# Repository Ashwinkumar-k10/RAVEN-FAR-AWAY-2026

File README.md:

# 🚁 RAVEN System (Rapid Autonomous Victim Emergency Network)

**RAVEN** is a next-generation, fully autonomous AI drone surveillance and emergency response system. Designed to dramatically reduce emergency response times, RAVEN utilizes edge-deployed computer vision and advanced Vision-Language Models (VLMs) to detect, verify, and broadcast severe vehicular collisions in real-time.

## 🌟 Key Features

- **Multi-Agent Verification Pipeline:** Utilizes a fine-tuned YOLOv8 model for real-time bounding box detection, cross-verified by a Moondream VLM to guarantee zero false positives on standing traffic.
- **Autonomous Emergency Dispatch:** Automatically assesses accident severity (Normal, Serious, Critical) and broadcasts live telemetry to the dashboard.
- **Live Command Center Dashboard:** A sleek, fully responsive HTML/JS command center featuring real-time WebSockets, OpenStreetMap integration, live video feeds, and an AI semantic analysis typewriter effect.
- **Text-to-Speech Status Updates:** Integrated Web Speech API provides hands-free, continuous audible situational awareness for operators.

## 🛠️ Technology Stack

- **Backend:** FastAPI, Python, SQLAlchemy, WebSockets
- **AI Models:** 
  - `YOLOv8` (Fine-tuned for collision and vehicle damage detection)
  - `Moondream` (Local VLM running via Ollama for semantic scene assessment)
- **Frontend:** Vanilla HTML5, CSS3, JavaScript
- **Mapping:** OpenStreetMap via Leaflet.js

## 🚀 Getting Started

### Prerequisites
- Python 3.10+
- [Ollama](https://ollama.ai/) installed locally
- Moondream model pulled (`ollama run moondream`)

### Installation

1. **Clone the repository:**
   ```bash
   git clone https://github.com/yourusername/raven-system.git
   cd raven-system
   ```

2. **Install dependencies:**
   Ensure you are in the `backend` or `firmware` environment:
   ```bash
   pip install -r firmware/requirements.txt
   ```

3. **Ensure Models are Present:**
   Make sure your fine-tuned YOLO model is placed in `models/best.pt`.

### 🏃‍♂️ Running the System

You can run the entire system instantly using the provided batch script:
```bash
./run_demo.bat
```
This script will:
1. Boot up the FastAPI backend on `http://localhost:8000`
2. Automatically open the live Command Center Dashboard in your default web browser.

**Using the Dashboard:**
- Click **Start Analysis** to commence the live AI video feed processing.
- Click **Enable Audio** to unlock the text-to-speech incident broadcasts.

## 🤝 Contributing
Built during a Hackathon! Pull requests and ideas for further autonomous response integration are always welcome.

## 📄 License
This project is licensed under the MIT License.

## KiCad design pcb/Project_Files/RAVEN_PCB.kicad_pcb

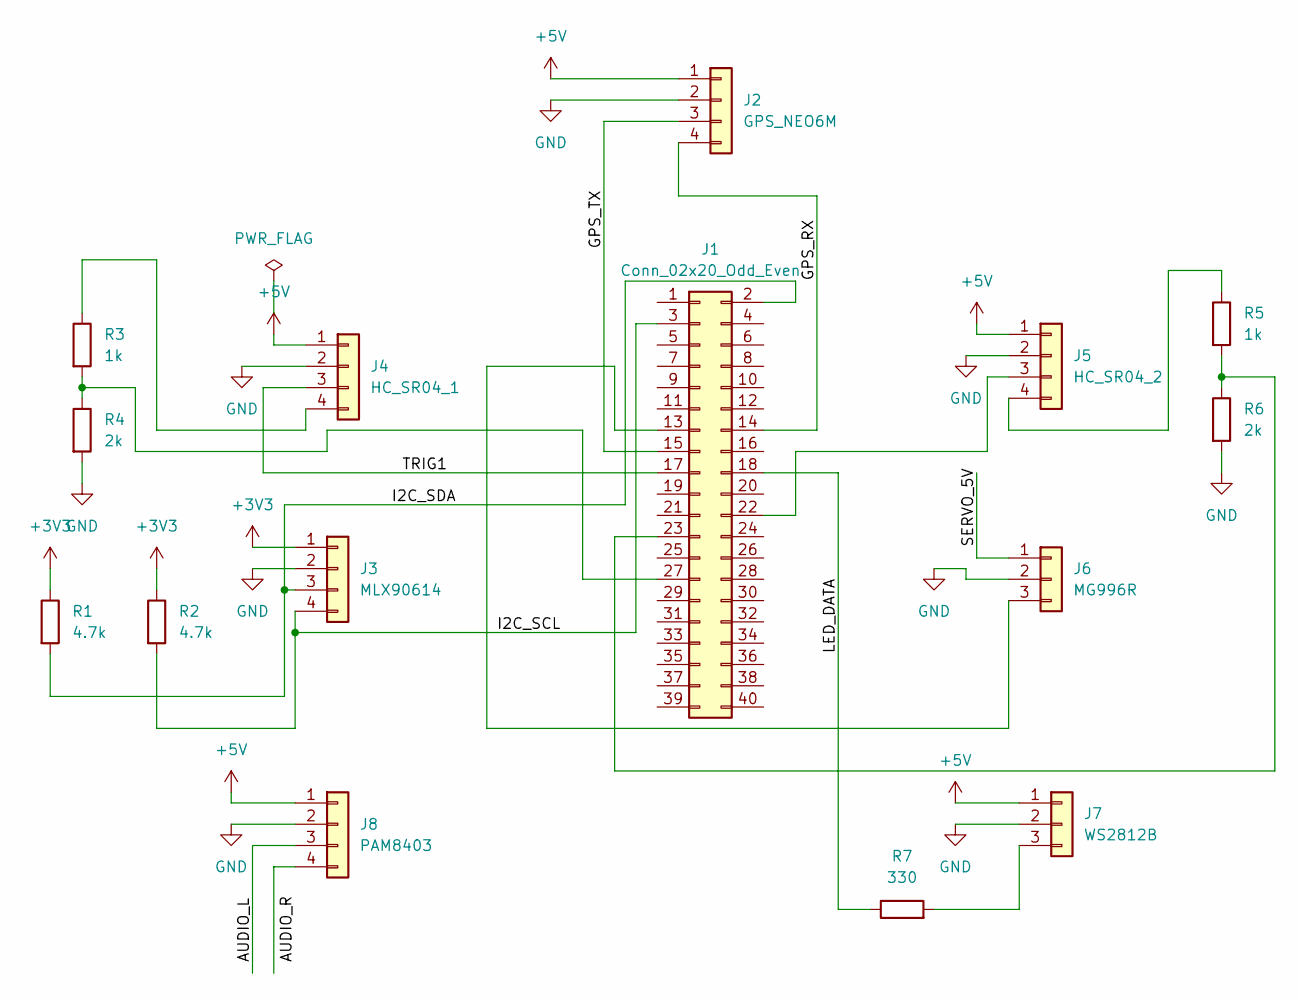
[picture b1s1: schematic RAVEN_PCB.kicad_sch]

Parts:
J1: Conn_02x20_Odd_Even; PinHeader_2x20_P2.54mm_Vertical
J2: GPS_NEO6M; PinHeader_1x04_P2.54mm_Vertical
J3: MLX90614; JST_XH_B4B-XH-A_1x04_P2.50mm_Vertical
J4: HC_SR04_1; JST_XH_B4B-XH-A_1x04_P2.50mm_Vertical
J5: HC_SR04_2; JST_XH_B4B-XH-A_1x04_P2.50mm_Vertical
J6: MG996R; PinHeader_1x03_P2.54mm_Vertical
J7: WS2812B; JST_XH_B3B-XH-A_1x03_P2.50mm_Vertical
J8: PAM8403; JST_XH_B4B-XH-A_1x04_P2.50mm_Vertical
R1, R2: 4.7k; R_Axial_DIN0207_L6.3mm_D2.5mm_P10.16mm_Horizontal
R3, R5: 1k; R_Axial_DIN0207_L6.3mm_D2.5mm_P10.16mm_Horizontal
R4, R6: 2k; R_Axial_DIN0207_L6.3mm_D2.5mm_P10.16mm_Horizontal
R7: 330; R_Axial_DIN0207_L6.3mm_D2.5mm_P10.16mm_Horizontal

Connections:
+3V3: J3.1, R1.1, R2.1
+5V: J2.1, J4.1, J5.1, J7.1, J8.1
/AUDIO_L: J8.3
/GPS_RX: J1.14, J2.4
/GPS_TX: J1.15, J2.3
/I2C_SCL: J1.3, J3.4, R2.2
/I2C_SDA: J1.2, J3.3, R1.2
/LED_DATA: J1.18, R7.1
/SERVO_5V: J6.1
/TRIG1: J1.17, J4.3
GND: J2.2, J3.2, J4.2, J5.2, J6.2, J7.2, J8.2, R4.2, R6.2
unnamed: J1.13, J6.3
unnamed: J1.22, J5.3
unnamed: J1.23, R5.2, R6.1
unnamed: J1.27, R3.2, R4.1
unnamed: J4.4, R3.1
unnamed: J5.4, R5.1
unnamed: J7.3, R7.2

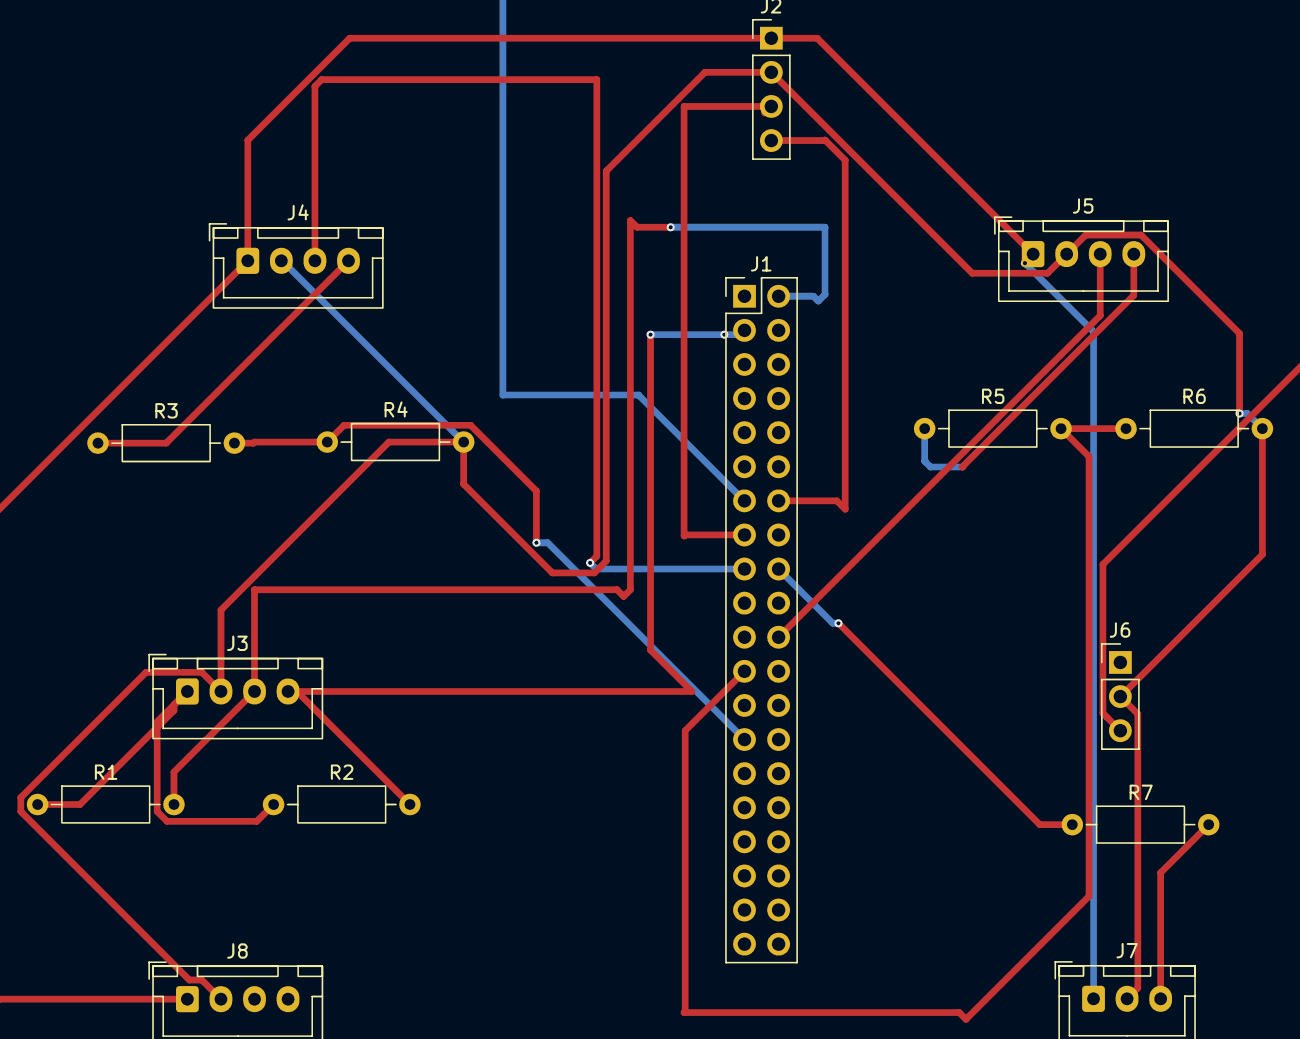
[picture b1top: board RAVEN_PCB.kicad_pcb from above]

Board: 2 copper layers, 15 parts (0 on the bottom side), 16 nets.

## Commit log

2026-06-11 Final Hackathon Version: Clean, lightweight upload
2026-06-11 Added RAVEN PCB design files
2026-06-11 Add RAVEN drone and payload bay CAD models
2026-06-11 feat(ml): add YOLOv8s best.pt and last.pt via Git LFS (mAP@50: 0.978)
2026-06-14 feat: add trained YOLOv8s weights to models/
2026-06-14 feat: add best.pt to models/

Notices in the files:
README.md:
License: MIT
